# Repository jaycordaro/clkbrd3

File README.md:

# clkbrd3
In 2021, even 32kHz oscillators are hard to come by!  
# Motivation
I built this board due to parts shortage and cost issues.  My friends at SiTime are quoting **86 week leadtime** for SiT1532 32.768kHz MEMS oscillators as of the end of July 2021 .  
Diodes KX321 32.768kHz crystal oscillators are currently available from DigiKey, albeit at $1.83 per unit in 1k quantities.  
The design objective for clkbrd3 was a very low-power, very low-cost crystal oscillator with a minimum of board area so it could be used in "always on" consumer electronics.  The circuit is from The Art of Electronics 3rd Edition by Horowitz & Hill, Section 7.1 figure 7-40.  U2 is in the Pierce configuration and has 10k resistors on power and ground to reduce cross conduction current.  U4 schmitt trigger inverter cleans up the signal and U5 amplifies it to 1.8V (or 2.5V or 3.3V) LVCMOS levels.  See H&H for more deails.  
# Results
Fabricated at [JLCPCB](URL "https://jlcpcb.com") July, 2021.  I originally tried LVC logic components, because they are cheaper, but they don't work below 1.65V and the current consumption was way too high.  
## Power 
I measured current consumption with a Keysight B2901A SMU. With AUP devices installed, I did measure higher current than what H&H quoted: 867nA for 0.9V 1st stage, and 4.54uA for 1.8V output driver for a total power consumption of 8.95uW.  I have not investigated the reason for the discrepancy.  Jitter performance is quite good, peak-to-peak jitter of around 3ns.  See the ./validation directory.
## Cost
Nexperia raised prices on the AUP devices after I bought them.

The BOM for the oscillator portion of the design is below:

Designator  | Description | Component | Cost 1k qty
------------ | -------------| ------------- | -------------
U4 | Schmitt Trigger Inv |SN74AUP1G14DCKR | $0.066
U2 | Unbuffered inverter | 74AUP1GU04GW,125 | $0.1059
U5 | Buffered inverter | SN74AUP1G04DCKR | $0.072
Y1 | through-hole xtal | TDXLF-206 32.768 | 0.0481
C5 | 0.1uF cap X7R 0402 | CC0402KRX7R9BB104 | $0.0031            
C8 | 0.1uF cap X7R 0402 | CC0402KRX7R9BB104| $0.0031
C10 | 0.1uF cap X7R 0402| CC0402KRX7R9BB104| $0.0031
C9 | 10n cap X7R 0402   | CGA2B2X7R1E103KT0Y0F | $0.0069
R4 | 10M ohm 0402 | 0402WGF1005TCE | $0.0007
R5 | 330k ohm 0402 | 0402WGJ0334TCE | $0.0005
C4 | 22pF 0402 C0G | CC0402JRNPO9BN220 | $0.001
C6 | 22pF 0402 C0G | CC0402JRNPO9BN220 | $0.001
R7 | 10M ohm 0402| 0402WGF1005TCE | $0.0007
R3 | 10kOhm resistor,0402| RC0603FR-0710KL | $0.0012
R2 | 10kOhm resistor,0402| RC0603FR-0710KL | $0.0012

that gives a component cost for the oscillator of $0.3155.  The price increased 8 cents from when I bought the parts in early July.  
Who says there is no inflation?
## Area
The actual oscillator area is 8mm x 8.3 mm, using a 4 layer stackup with signals and components placed on top and bottom.  Smaller packages would make the area much smaller but carry a cost adder.  A rant on 4-layer boards.  The JLCPCB boards were $2 for 5 boards?  Why would anyone build 2 layer boards at that price?
# Instructions
## To Edit
To edit the schematic or layout, or use in your own projects, clone the repo.  
note that KiCAD 5 gets confused, I think because of the 10k resistors on power nets.  If you look at the layout there appears to be a problem but I just ignored it and fabbe the board and it worked fine.
## To Build
To just build it as-is, use the zip file in ./gerbers and upload it to jlcpcb.
# Operation
Board is a low current consumption 32kHz crystal oscillator.  see the schematic in the ./schematic directory.  For convenience, the board can be powered by a 5V USB Micro connector or a 5V barrel jack.  U1 and U3 are LDOs, not low-power, low-Iq or cheap, but convenient.  RV1 and RV2 are potentiometers to set the voltage for VXTAL and VDDIO.  
J3 selects whether to use a 5V barrel jack (J3 == 2-3) or micro USB (J3 == 2-1).  Adjust RV1 to provide 1.8V on VDDIO (J5 pin 1) and adjust RV2 to provide 0.9V on J8.1.  32kHz clock output is available on J6.1 or J7 SMA connector, if installed.  
If the potentiometers are removed, the board can be powered from lab supplies to measure current.  
# Validation 
Validation files are in the ./validation directory.  Performance is quite good, although startup time is over half a second.
The sub $0.05 crystal performed well actually.  Jitter was very low.  The MDA photos show a deterministic variation of the frequency.  I should look into what's going on here, and if this can be improved without increasing power consumption.
# Conclusion
You can build a low-power 32kHz oscillator out of discrete components for much less than the current cost of a crystal oscillator.  Performance is good, as long as the startup time is not critical.

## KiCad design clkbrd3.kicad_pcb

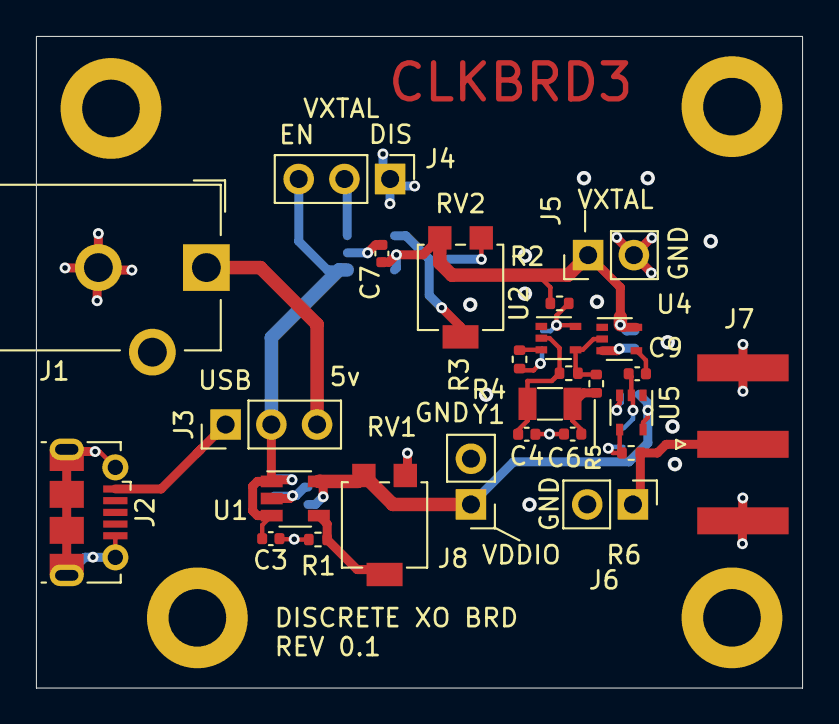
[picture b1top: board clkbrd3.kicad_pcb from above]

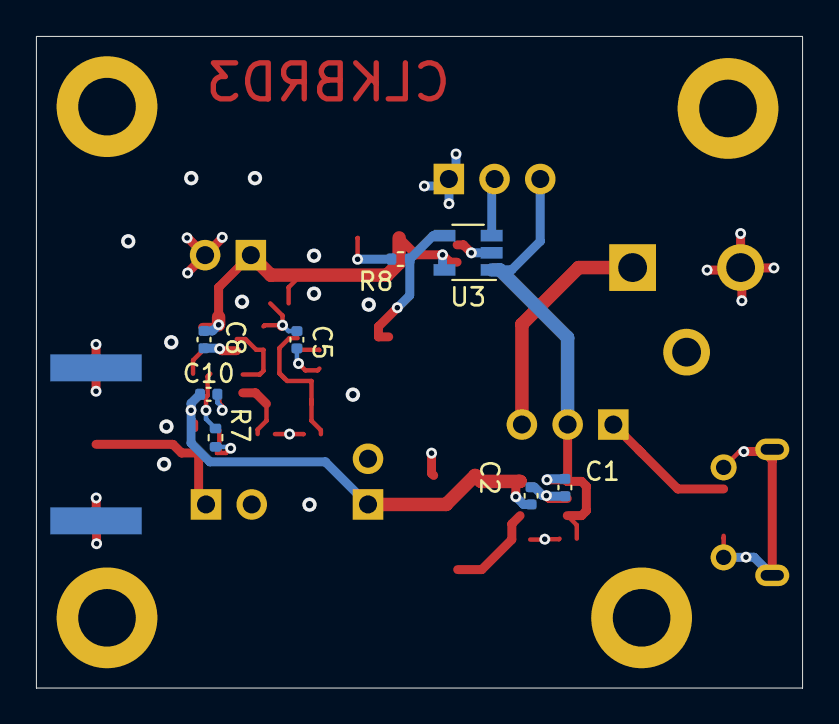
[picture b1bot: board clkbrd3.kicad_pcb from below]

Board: 4 copper layers, 42.6 x 36.2 mm, 38 parts (8 on the bottom side), 15 nets.

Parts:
C1, C2, C3, C7: 1u; C_0402_1005Metric
C4, C6: 22p; C_0402_1005Metric
C5, C8, C10: 0.1u; C_0402_1005Metric
C9: 10n; C_0402_1005Metric
H1, H2, H3, H4: MountingHole_Pad; MountingHole_3.2mm_M3_DIN965_Pad
J1: Barrel_Jack; BarrelJack_CUI_PJ-102AH_Horizontal
J2: USB_B_Micro; USB_Micro-B_Molex-105017-0001
J3: pwr_input_select; PinHeader_1x03_P2.54mm_Vertical
J4: 0.9v enable; PinHeader_1x03_P2.54mm_Vertical
J5: vddio_header; PinHeader_1x02_P2.54mm_Vertical
J6: clock output header; PinHeader_1x02_P2.54mm_Vertical
J7: Conn_Coaxial; SMA_Amphenol_132289_EdgeMount
J8: vxtal_header; PinHeader_1x02_P2.54mm_Vertical
R1, R8: 59k; R_0402_1005Metric
R2, R3: 10k; R_0402_1005Metric
R4, R7: 10M; R_0402_1005Metric
R5: 330k; R_0402_1005Metric
R6: 0; R_0402_1005Metric
RV1, RV2: 50k; Potentiometer_Bourns_3314G_Vertical
U1, U3: ADP1710AUJZ-R7; TSOT-23-5
U2: 74AUP1GU04; SOT-353_SC-70-5
U4: 74AUP1G14; SOT-353_SC-70-5
U5: 74LVC1G04; SOT-353_SC-70-5
Y1: Crystal; Crystal_SMD_3215-2Pin_3.2x1.5mm

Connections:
+1V8: C2.2, C5.2, C7.2, C8.1, C10.1, J5.1, J8.1, R2.1, R2.2, RV1.3, RV2.3, U1.5, U2.5, U3.5, U4.5, U5.5
GND: C1.1, C2.1, C3.1, C4.2, C5.1, C6.2, C7.1, C8.2, C10.2, H1.1, H2.1, H3.1, H4.1, J1.2, J2.5, J2.6, J4.1, J5.2, J6.2, J7.2, J8.2, R1.1, R3.1, R3.2, R8.1, RV1.1, RV2.1, U1.2, U2.3, U3.2, U4.3, U5.3
unnamed: C1.2, C3.2, J3.2, J4.3, U1.1, U1.3, U3.1
unnamed: C4.1, R4.2, U2.2, Y1.1
unnamed: C6.1, R5.1, Y1.2
unnamed: C9.1, R7.1, U5.2
unnamed: C9.2, U4.4
unnamed: J1.1, J3.3
unnamed: J2.1, J3.1
unnamed: J4.2, U3.3
unnamed: J6.1, J7.1, R6.2
unnamed: R1.2, RV1.2, U1.4
unnamed: R4.1, R5.2, U2.4, U4.2
unnamed: R6.1, R7.2, U5.4
unnamed: R8.2, RV2.2, U3.4

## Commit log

2021-07-31 PDF of Schematic
2021-08-01 add gerber and drill files for JLCPCB fabrication
2021-08-01 added files
